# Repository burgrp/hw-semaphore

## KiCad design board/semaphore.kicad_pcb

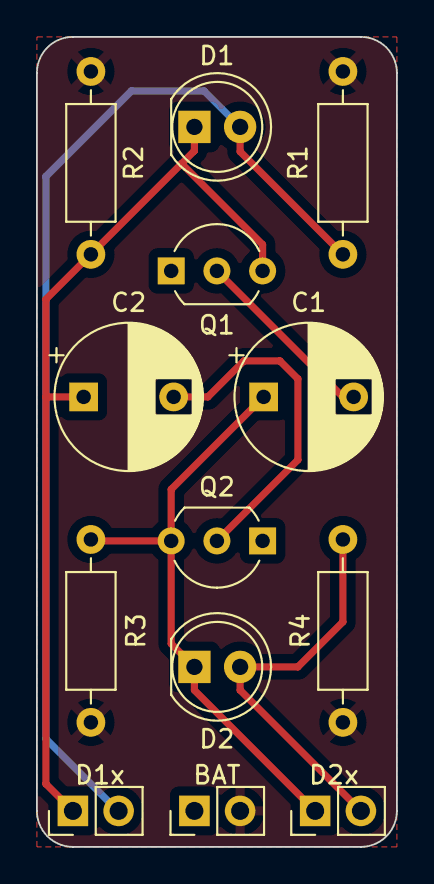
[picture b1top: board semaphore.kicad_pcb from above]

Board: 2 copper layers, 20.0 x 45.0 mm, 13 parts (0 on the bottom side), 8 nets.

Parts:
C1, C2: 10u; CP_Radial_D8.0mm_P5.00mm
D1, D2: LED; LED_D5.0mm
J1: BAT; PinHeader_1x02_P2.54mm_Vertical
J2: D1x; PinHeader_1x02_P2.54mm_Vertical
J3: D2x; PinHeader_1x02_P2.54mm_Vertical
Q1, Q2: 2N3904; TO-92_Inline_Wide
R1, R4: 270R; R_Axial_DIN0207_L6.3mm_D2.5mm_P10.16mm_Horizontal
R2, R3: 10k; R_Axial_DIN0207_L6.3mm_D2.5mm_P10.16mm_Horizontal

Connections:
/BAT+: J1.2, R1.1, R2.1, R3.1, R4.1
/BAT-: J1.1, Q1.1 (E), Q2.1 (E)
/D1+: D1.2 (A), J2.2, R1.2
/D1-: C2.1, D1.1 (K), J2.1, Q1.3 (C), R2.2
/D2+: D2.2 (A), J3.2, R4.2
/D2-: C1.1, D2.1 (K), J3.1, Q2.3 (C), R3.2
unnamed: C1.2, Q1.2 (B)
unnamed: C2.2, Q2.2 (B)
